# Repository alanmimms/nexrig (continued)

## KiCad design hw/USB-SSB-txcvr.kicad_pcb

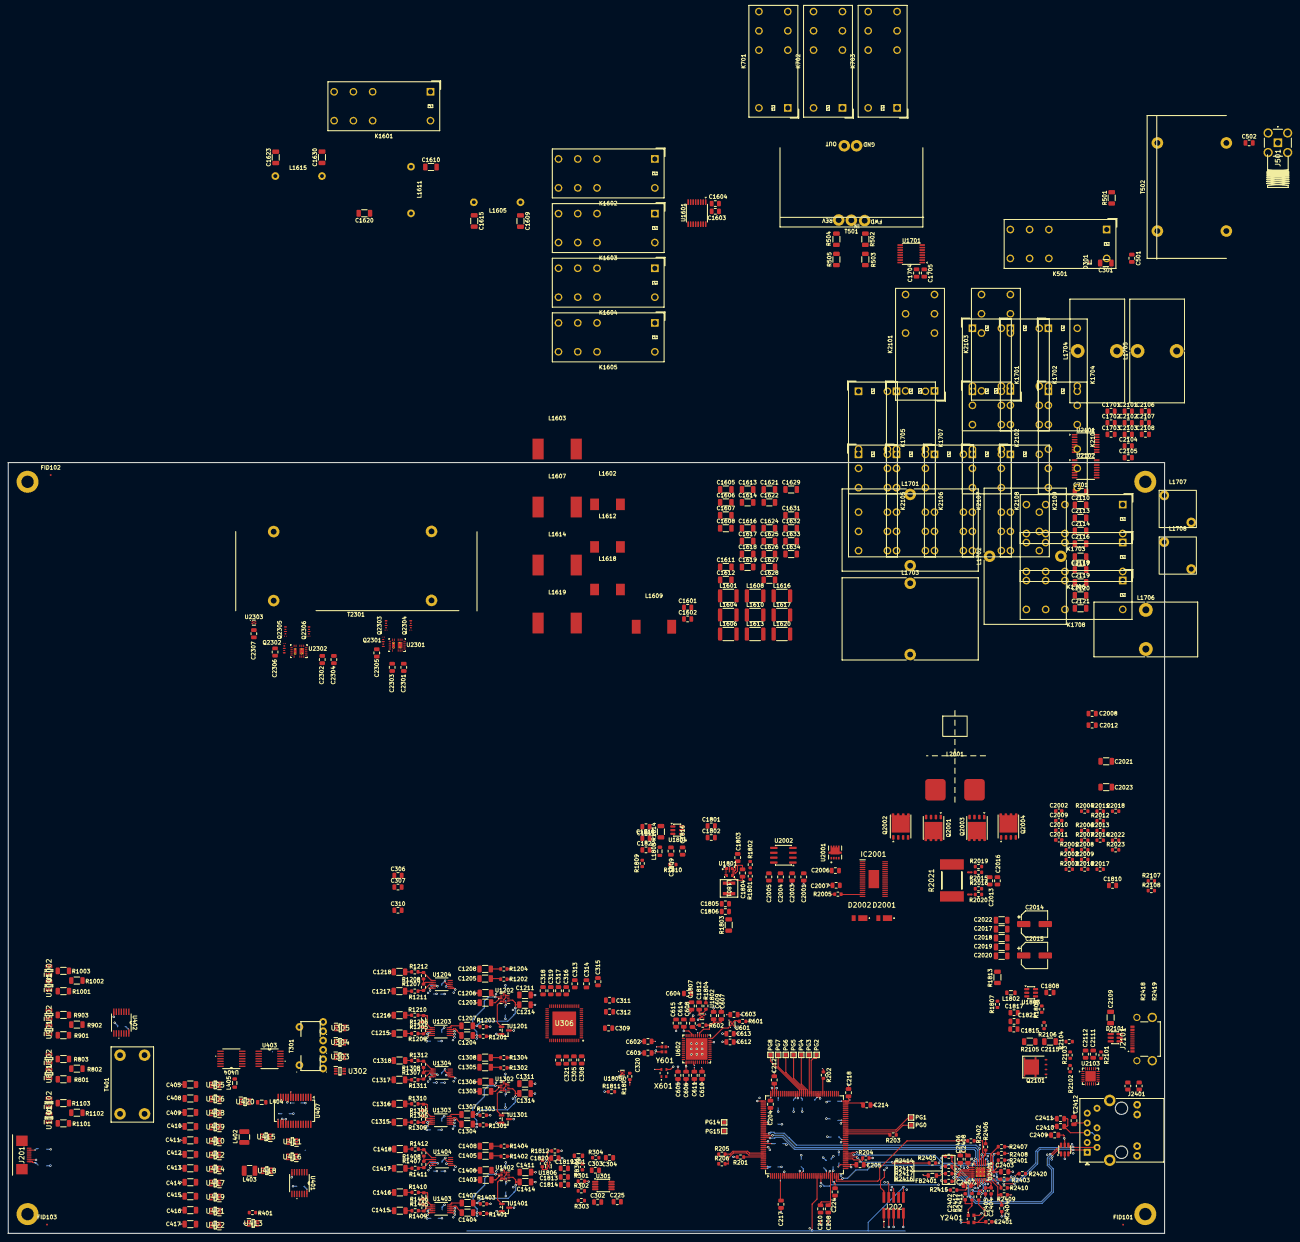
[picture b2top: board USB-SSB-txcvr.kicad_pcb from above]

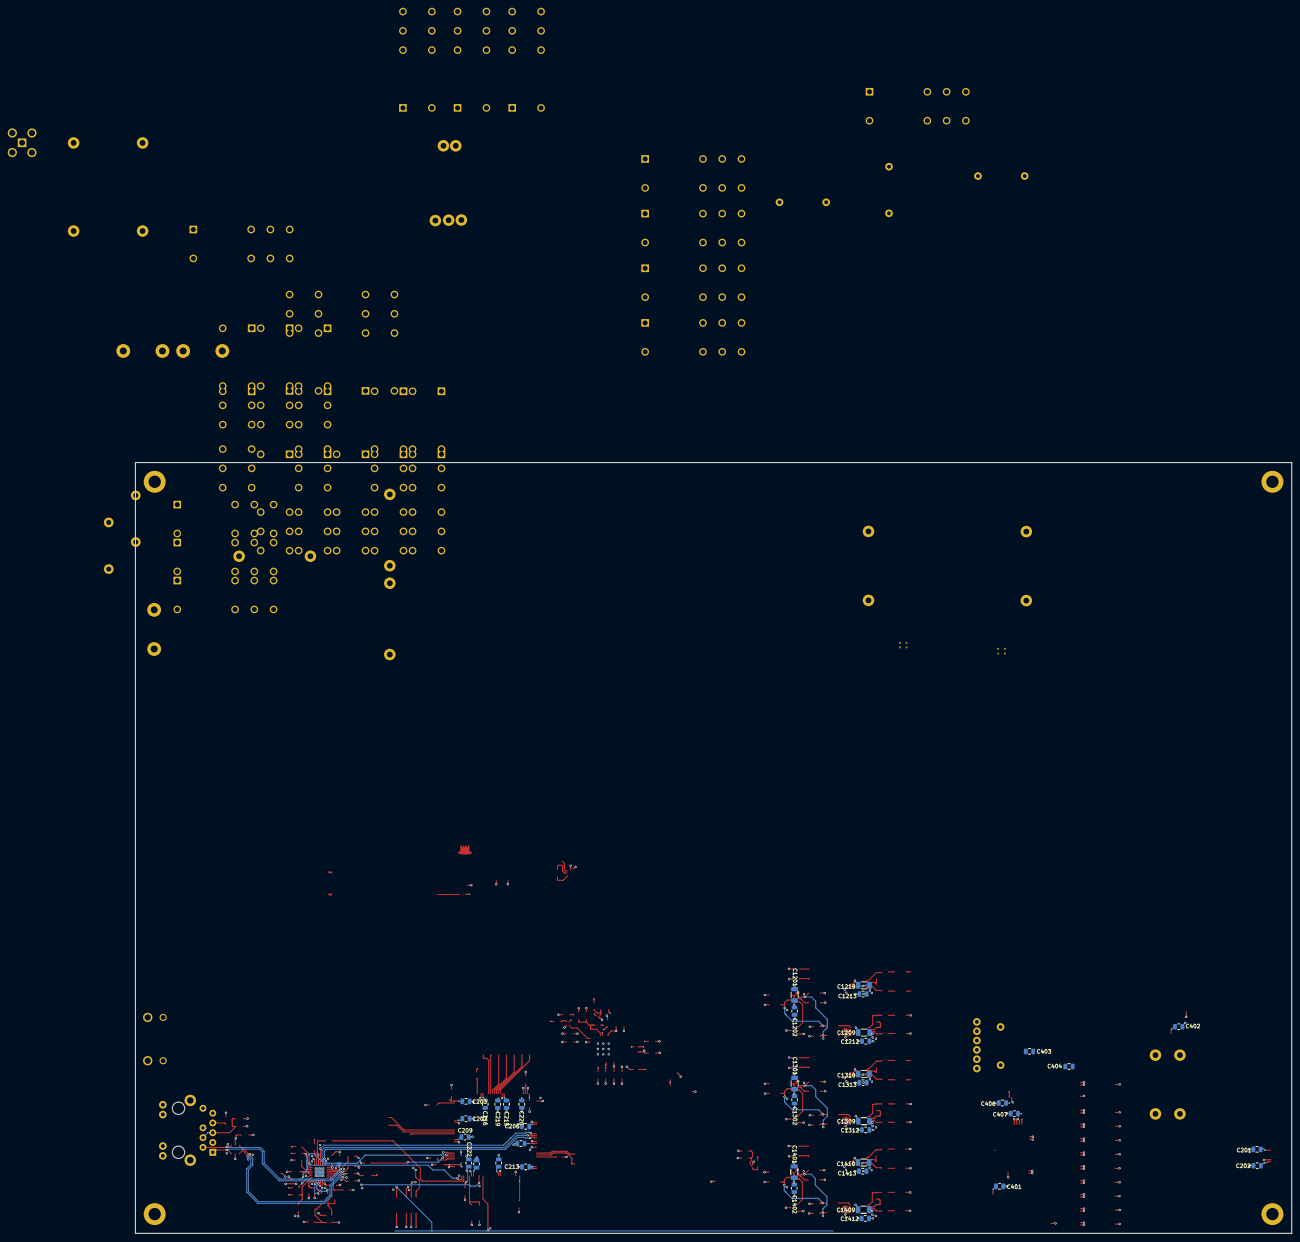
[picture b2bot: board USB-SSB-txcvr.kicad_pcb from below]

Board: 6 copper layers, 300.0 x 200.0 mm, 573 parts (39 on the bottom side), 399 nets.

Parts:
C201, C202, C204, C205, C305, C309, C312, C314, C501, C1601, C1602, C1603, C1701, C1702, C1703, C1704, C1817, C1818, C1821, C1822, C2005, C2101, C2102, C2103, C2104, C2105, C2107, C2406: 10uF; C_0805_2012Metric
C203: 100uF; C_0805_2012Metric
C206, C207, C208, C210, C212, C214, C217, C218, C219, C220, C221, C222, C224, C225, C302, C304, C308, C310, C311, C313, C315, C316, C318, C321, C602, C608, C609, C613, C615, C1202, C1212, C1213, C1302, C1312, C1313, C1402, C1412, C1413, C1804, C1815, C1816, C2003, C2007, C2008, C2012, C2301, C2302, C2403, C2407, C2408, C2409, C2410, C2411: 0.1uF; C_0805_2012Metric
C209, C216, C223, C307, C320, C401, C402, C403, C404, C406, C407, C601, C603, C604, C1803, C1807, C1812, C1813, C1814, C1819, C1820, C2307: 1uF; C_0805_2012Metric
C211, C1604, C1705, C2106, C2108: 100nF; C_0805_2012Metric
C213, C215, C303, C306, C2303, C2304: 2.2uF; C_0805_2012Metric
C301: 1uF 250V; C_1206_3216Metric
C317, C319, C605, C607, C612, C614, C2006, C2111, C2112: 4.7uF; C_0805_2012Metric
C405: 4pF; C_1206_3216Metric
C408: 8pF; C_1206_3216Metric
C409: 16pF; C_1206_3216Metric
C410: 32pF; C_1206_3216Metric
C411: 64pF; C_1206_3216Metric
C412: 128pF; C_1206_3216Metric
C413: 256pF; C_1206_3216Metric
C414: 512pF; C_1206_3216Metric
C415: 1024pF; C_1206_3216Metric
C416: 2048pF; C_1206_3216Metric
C417: 2.2nF; C_1206_3216Metric
C502: 10uF 500V; C_0805_2012Metric
C606: .1uF; C_0805_2012Metric
C610, C2001: 10nF; C_0805_2012Metric
C611: 1nF; C_0805_2012Metric
C701, C1201, C1301, C1401, C2021, C2023: 10uF; C_1206_3216Metric
C1203, C1206, C1211, C1214, C1303, C1306, C1311, C1314, C1403, C1406, C1411, C1414: 2.2uF; C_1206_3216Metric
C1204, C1205, C1207, C1208, C1209, C1210, C1304, C1305, C1307, C1308, C1309, C1310, C1404, C1405, C1407, C1408, C1409, C1410, C2017, C2018, C2019, C2020, C2022: 1uF; C_1206_3216Metric
C1215, C1216, C1217, C1218, C1315, C1316, C1317, C1318, C1415, C1416, C1417, C1418: 3.3nF; C_1206_3216Metric
C1605, C1633: 39pF; C_1206_3216Metric
C1606, C1611, C1621, C1632: 150pF; C_1206_3216Metric
C1607, C1634: 75pF; C_1206_3216Metric
C1608, C1619, C1622, C1631: 27pF; C_1206_3216Metric
C1609, C1630: 360pF; C_1206_3216Metric
C1610, C1620: 330pF; C_1206_3216Metric
C1612, C1629: 62pF; C_1206_3216Metric
C1613, C1628: 33pF; C_1206_3216Metric
C1614, C1626: 24pF; C_1206_3216Metric
C1615, C1623: 300pF; C_1206_3216Metric
C1616, C1624: 120pF; C_1206_3216Metric
C1617, C1627: 68pF; C_1206_3216Metric
C1618, C1625: 36pF; C_1206_3216Metric
C1801: 4.7uF 50V; C_0805_2012Metric
C1802: 0.1uF 50V; C_0805_2012Metric
C1805, C1806: 22uF; C_0805_2012Metric
C1808, C1809, C1810, C1811: 1uF 50V; C_0805_2012Metric
C2002, C2011: 100pF; C_0603_1608Metric
C2004, C2305, C2306: 3.3nF; C_0805_2012Metric
C2009, C2010: 0.22uF; C_0603_1608Metric
C2013: 220pF; C_0805_2012Metric
C2014, C2015: 10uF; CP_Elec_6.3x5.4
C2016: 470pF; C_0805_2012Metric
C2109: 4.7uF 50V; C_1206_3216Metric
C2110: 1280pF; C_1206_3216Metric
C2113: 640pF; C_1206_3216Metric
C2114: 320pF; C_1206_3216Metric
C2115: 0.1uF 50V; C_1206_3216Metric
C2116: 160pF; C_1206_3216Metric
C2117: 80pF; C_1206_3216Metric
C2118: 40pF; C_1206_3216Metric
C2119: 20pF; C_1206_3216Metric
C2120: 10pF; C_1206_3216Metric
C2121: 5pF; C_1206_3216Metric
C2401, C2402: 8.2pF; C_0603_1608Metric
C2404: 1uF; C_0603_1608Metric
C2405: 470pF; C_0603_1608Metric
C2412: 1000pF; C_0805_2012Metric
D301: STS321150B100AH; Infineon_SG-WLL-2-3_0.58x0.28_P0.36mm
D2001, D2002: DFLS1200-7; DFLS12007
D2101: MMQA33VT1G; SC-74-6_1.55x2.9mm_P0.95mm
FB301: 600; L_0603_1608Metric
FB2401: BLM21AG102SN1D; L_0805_2012Metric
FID101, FID102, FID103: Fiducial; Fiducial_0.5mm_Mask2mm
IC2001: LTC3779IFE#PBF; SOP50P640X120-39N
J201: 68710814022
J202: FTSH-105-01-L-DV-K; FTSH10501LDVK
J501: SMA; RFPCSMA27F
J2101: USB C power only; UJ20CHGMSMT4P16TR
J2401: RJ45_Abracon_ARJP11A-MASA-B-A-EMU2; RJ45_Abracon_ARJP11A-MA_Horizontal
K501, K701, K702, K703, K1601, K1602, K1603, K1604, K1605, K1701, K1702, K1703, K1704, K1705, K1706, K1707, K1708, K2101, K2102, K2103, K2104, K2105, K2106, K2107, K2108, K2109: G2RL-2; Relay_DPDT_Omron_G2RL-2
L301: 1.2uH; L_0805_2012Metric
L402: 8.2uH; L_1210_3225Metric
L403: 2.7uH; L_1210_3225Metric
L404: 820nH; L_0805_2012Metric
L405: 270nH; L_0805_2012Metric
L1601, L1604, L1616, L1620: 1.2uH; L_1812_4532Metric
L1602, L1618: 3.3uH; L_Wurth_8.4mm_sq_SMT
L1603, L1607, L1614, L1619: 3.9uH; L_Wurth_12.1mm_sq_SMT
L1605, L1615: 17.4uH; toroid-inductor-t80-2
L1606, L1610, L1617: 1.5uH; L_1812_4532Metric
L1608, L1613: 1uH; L_1812_4532Metric
L1609: 8.2uH; L_Wurth_10.9mm_sq_SMT
L1611: 19.1uH; toroid-inductor-t80-2
L1612: 4.7uH; L_Wurth_8.4mm_sq_SMT
L1701: 64uH; L_Toroid_Vertical_L35.1mm_W21.1mm_P18.50mm_Vishay_TJ6
L1702: 32uH; L_Toroid_Vertical_L35.1mm_W21.1mm_P18.50mm_Vishay_TJ6
L1703: 16uH; L_Toroid_Vertical_L35.1mm_W21.1mm_P18.50mm_Vishay_TJ6
L1704: 8uH; L_Toroid_Vertical_L26.7mm_W14.0mm_P10.16mm_Pulse_D
L1705: 4uH; L_Toroid_Vertical_L26.7mm_W14.0mm_P10.16mm_Pulse_D
L1706: 2uH; L_Toroid_Vertical_L26.7mm_W14.0mm_P10.16mm_Pulse_D
L1707: 1uH; Coilcraft-uni10
L1708: 0.5uH; Coilcraft-uni10
L1801: 2.2uH; IND_XGL4030_COC
L1802: 2.2uH; L_0805_2012Metric
L1803: 3.3uH; L_0805_2012Metric
L2001: 6.8uH; Bourns PQ2614BLA-6R8K
MH101, MH102, MH103, MH104: MountingHole; MountingHole_3.2mm_M3_ISO7380_Pad
NT2001, NT2002: NetTie_2; NetTie-2_SMD_Pad0.5mm
PG201: PG0; TestPoint_Pad_1.0x1.0mm
PG202: PG1; TestPoint_Pad_1.0x1.0mm
PG203: PG2; TestPoint_Pad_1.0x1.0mm
PG204: PG3; TestPoint_Pad_1.0x1.0mm
PG205: PG4; TestPoint_Pad_1.0x1.0mm
PG206: PG5; TestPoint_Pad_1.0x1.0mm
PG207: PG6; TestPoint_Pad_1.0x1.0mm
PG208: PG7; TestPoint_Pad_1.0x1.0mm
PG209: PG8; TestPoint_Pad_1.0x1.0mm
PG210: PG14; TestPoint_Pad_1.0x1.0mm
PG211: PG15; TestPoint_Pad_1.0x1.0mm
Q2001, Q2002, Q2003, Q2004: BSC360N15NS3 G; Infineon_PG-TDSON-8_6.15x5.15mm
Q2101: SQJ433EP; PowerPAK_SO-8L_Single
Q2301, Q2302, Q2303, Q2304, Q2305, Q2306: EPC2207; EPC2207-GaN-FET
R201, R202, R203, R204, R205, R206, R303, R304, R1201, R1202, R1203, R1204, R1205, R1206, R1207, R1208, R1301, R1302, R1303, R1304, R1305, R1306, R1307, R1308, R1401, R1402, R1403, R1404, R1405, R1406, R1407, R1408, R2002, R2005, R2008, R2108, R2401, R2406, R2408, R2409, R2410, R2420: 10k; R_0603_1608Metric
R301, R302, R2012, R2013, R2101, R2106: 1k; R_0603_1608Metric
R401: 6.8; R_0603_1608Metric
R501: 49.9; R_1206_3216Metric
R502, R504: 47k; R_1206_3216Metric
R503, R505: 220; R_1206_3216Metric
R601, R1804, R1805, R1806, R1811, R1812, R2411, R2412: 0; R_0603_1608Metric
R602, R2015, R2016, R2019, R2020, R2104: 100; R_0603_1608Metric
R801, R803, R901, R903, R1001, R1003, R1101, R1103: 34; R_1206_3216Metric
R802, R902, R1002, R1102: 562; R_1206_3216Metric
R1209, R1210, R1211, R1212, R1309, R1310, R1311, R1312, R1409, R1410, R1411, R1412: 330; R_0603_1608Metric
R1801: 60.4k; R_0603_1608Metric
R1802, R2415: 12.1k; R_0603_1608Metric
R1803, R1813, R1814, R2105: 0; R_1206_3216Metric
R1807, R1809, R2003, R2009, R2102, R2107, R2407: 100k; R_0603_1608Metric
R1808: 22.1k; R_0603_1608Metric
R1810: 13.7k; R_0603_1608Metric
R2001: 649k; R_0603_1608Metric
R2004, R2010: 3.53k; R_0603_1608Metric
R2006: 13k; R_0603_1608Metric
R2007: 125k; R_0603_1608Metric
R2011: 107k; R_0603_1608Metric
R2014: 5; R_0603_1608Metric
R2017, R2018, R2022, R2023: 2; R_0603_1608Metric
R2021: 5m; CSS2H3920K5L00F
R2103: 22k; R_0603_1608Metric
R2402, R2403, R2404, R2405: 33; R_0603_1608Metric
R2413, R2414, R2416, R2417: 49.9; R_0603_1608Metric
R2418, R2419: 270; R_0805_2012Metric
T301: 12t primary : 6T #26 trifilar secondary FT37-43; Toroid-1pri-3sec-ft50
T401: 8t bifilar; 200-800-transformer-FT50
T501: 2xFT140-stacked-bruene
T502: 16t:8t bifilar #18AWG FT140-43; 2xFT140-stacked
T2301: 2xFT240-stacked
U201: STM32H753ZIT6; LQFP-144_20x20mm_P0.5mm
U301: OPA1692xDGK; VSSOP-8_3x3mm_P0.65mm
U302: SOT65P220X110-6N
U303, U304, U305, U405, U406, U408, U409, U410, U411, U412, U413, U414, U415, U416, U417, U418, U419, U420, U421, U422, U801, U802, U901, U902, U1001, U1002, U1101, U1102: AS183-92LF; SOT65P220X110-6N
U306: AK5578EN; QFN50P900X900X100-65N
U401, U402, U403, U404: SN74LVC04APW; PW14
U407: MCP23S17_SS; SSOP-28_5.3x10.2mm_P0.65mm
U601: TPS7A2025PDQN; Texas_X2SON-4_1x1mm_P0.65mm
U602: ICE40UP5K-SG48ITR; QFN-48-1EP_7x7mm_P0.5mm_EP5.6x5.6mm
U1201, U1301, U1401: SZNUP1105LT1G; SOT-23
U1202, U1302, U1402: TS3A4751RUCR; TS3A4751-RUC14
U1203, U1204, U1303, U1304, U1403, U1404: MAX9939AUB+T; 21-0061L_MXM
U1601, U1701, U2101, U2102: TLC6C598PW; TSSOP-16_4.4x5mm_P0.65mm
U1801: LMR43610R3RPER; RPE0009A-MFG
U1802: TPS7A2012DQN; Texas_X2SON-4_1x1mm_P0.65mm
U1803, U1804: LMR51430; SOT-23-6
U1805: TPS7A92050DBVR; Texas_X2SON-4_1x1mm_P0.65mm
U1806: TPS7A2033DQN; Texas_X2SON-4_1x1mm_P0.65mm
U2001: NVTFS6H888NLTAG; WDFN_8NLTAG_ONS
U2002: TLV9062xD; SOIC-8_3.9x4.9mm_P1.27mm
U2103: STUSB4500QTR; QFN-24-1EP_4x4mm_P0.5mm_EP2.7x2.7mm
U2301, U2302: LMG1210RVRR; RVR0019A
U2303: TMP110D; Texas_X2SON-5_0.8x0.8mm_P0.48mm
U2401: LAN8742A; VQFN-24-1EP_4x4mm_P0.5mm_EP2.5x2.5mm_ThermalVias
U2402: USBLC6-4SC6; SOT-23-6
X601: XC8102AA01NR-G; XC8102AA01NRG
Y601: ECS-TXO-2016-33-400-TR; ECSTXO201633400TR
Y2401: ECS-250-8-37B2-RWN; ECS2033250BN

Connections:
+2.7V: C2112.1, U2103.23 (VREG_2V7)
+3.3V: C201.1, C202.1, C203.1, C204.1, C205.1, C206.1, C207.1, C208.1, C210.1, C212.1, C214.1, C216.1, C217.1, C218.1, C219.1, C220.1, C221.1, C222.1, C224.1, C310.1, C316.2, C317.2, C320.1, C321.1, C401.2, C402.2, C403.2, C404.2, C406.1, C407.1, C601.1, C602.1, C603.1, C1603.2, C1604.2, C1704.2, C1705.2, C1807.1, C2104.2, C2106.2, C2107.2, C2108.2, C2307.1, C2403.1, FB2401.1, J201.2, J201.8, J202.1 (VTref), R202.1, R203.1, R204.1, R205.1, R601.1, R1805.1, R1806.1, R1813.1, R2005.1, R2108.1, R2406.2, R2407.2, R2408.2, R2409.2, R2410.2, U201.6 (VBAT), U201.17 (VDD), U201.30 (VDD), U201.39 (VDD), U201.52 (VDD), U201.62 (VDD), U201.72 (VDD), U201.84 (VDD), U201.95 (VDD33USB), U201.108 (VDD), U201.121 (VDD), U201.131 (VDD), U201.143 (PDR_ON), U201.144 (VDD), U302.5 (V), U306.25 (TVDD), U306.30 (PW1), U306.31 (PW2), U306.32 (MSN), U306.51 (TDM0), U306.52 (TDM1), U306.54 (I2C), U306.57 (LDOE), U306.58 (ODP), U401.14 (VCC), U402.14 (VCC), U403.14 (VCC), U404.14 (VCC), U407.9 (VDD), U407.15 (A0), U601.4 (IN), U1601.1 (VCC), U1601.7 (~CLR), U1601.8 (~G), U1701.1 (VCC), U1701.7 (~CLR), U1701.8 (~G), U1802.4 (IN), U2101.1 (VCC), U2101.7 (~CLR), U2101.8 (~G), U2102.1 (VCC), U2102.7 (~CLR), U2102.8 (~G), U2303.5 (V+), U2401.9 (VDDIO), X601.4 (VIN), Y601.1 (TRI-STATE), Y601.4 (VDD)
+3.3VA: C223.1, C225.1, C1201.1, C1202.1, C1301.1, C1302.1, C1401.1, C1402.1, R301.2, R1812.1, U201.33 (VDDA), U1201.3, U1202.14 (V+), U1301.3, U1302.14 (V+), U1401.3, U1402.14 (V+)
+3.3VFPGAIO: C605.1, C606.1, C612.1, C613.1, C614.1, C615.1, U602.1 (VCCIO_2), U602.22 (SPI_VCCIO1), U602.33 (VCCIO_0), X601.3 (VOUT)
+5V: C501.1, C701.2, C1601.1, C1602.1, C1701.1, C1702.1, C1703.1, C2101.1, C2102.1, C2103.1, C2105.2, C2301.1, C2302.1, C2303.1, C2304.1, K501.12, Q2301.2 (S), Q2301.4 (S), Q2302.2 (S), Q2302.4 (S), R1814.1, U2301.2 (VIN), U2301.4 (VCC), U2301.5 (DHL), U2301.6 (DLH), U2302.2 (VIN), U2302.4 (VCC), U2302.5 (DHL), U2302.6 (DLH)
+5VA: C302.1, C1209.1, C1210.1, C1212.1, C1213.1, C1309.1, C1310.1, C1312.1, C1313.1, C1409.1, C1410.1, C1412.1, C1413.1, C2001.1, C2003.1, C2005.1, R1811.1, U301.8 (V+), U306.2 (AVDD1), U306.15 (AVDD2), U1203.9 (VCC), U1204.9 (VCC), U1303.9 (VCC), U1304.9 (VCC), U1403.9 (VCC), U1404.9 (VCC), U2002.8 (V+)
+6V: C1813.1, C1814.1, R1803.1, U1805.4 (IN), U1806.4 (IN)
/FPGA/CDONE: U201.141 (PE0), U602.7 (CDONE)
/FPGA/Ctrl.audioReset: R206.1, U201.42 (PA6), U306.28 (PDN)
/FPGA/Ctrl.audioSCL: R202.2, U201.81 (PD12), U306.45 (CKS2/SCL/CCLK)
/FPGA/Ctrl.audioSDA: R203.2, U201.55 (PF15), U306.43 (CKS0/SDA/CDTI)
/FPGA/Ctrl.enFPGAIOVdd: U201.18 (PF6), X601.1 (CE)
/FPGA/Ctrl.enable5V: U201.26 (PC0), U1804.5 (EN)
/FPGA/Ctrl.enable6V: U201.53 (PF13), U1801.3 (EN_UVLO)
/FPGA/Ctrl.qsdBCLK: U201.4 (PE5), U306.33 (BICK/DCLK)
/FPGA/Ctrl.qsdData: U201.5 (PE6), U306.36 (SDTO1/DSDOL2)
/FPGA/Ctrl.qsdMCLK: U306.24 (MCLK), U602.12 (IOB_22a)
/FPGA/Ctrl.qsdMOSI: U201.67 (PE14), U1203.2 (DIN), U1204.2 (DIN), U1303.2 (DIN), U1304.2 (DIN), U1403.2 (DIN), U1404.2 (DIN)
/FPGA/Ctrl.qsdNSS: U201.64 (PE11), U1203.10 (*CS), U1204.10 (*CS), U1303.10 (*CS), U1304.10 (*CS), U1403.10 (*CS), U1404.10 (*CS)
/FPGA/Ctrl.qsdPh0a: U602.6 (IOB_13b), U1402.1 (NO1)
/FPGA/Ctrl.qsdPh1a: U602.21 (IOB_23b), U1202.1 (NO1)
/FPGA/Ctrl.qsdPh2a: U602.45 (IOB_5b), U1302.1 (NO1)
/FPGA/Ctrl.qsdPh2b: U602.2 (IOB_6a), U602.9 (IOB_16a), U602.13 (IOB_24a), U1202.3 (NO2), U1302.3 (NO2), U1402.3 (NO2)
/FPGA/Ctrl.qsdPh2c: U602.4 (IOB_8a), U602.10 (IOB_18a), U602.20 (IOB_25b_G3), U1202.8 (NO3), U1302.8 (NO3), U1402.8 (NO3)
/FPGA/Ctrl.qsdPh2d: U602.3 (IOB_9b), U602.11 (IOB_20a), U602.19 (IOB_29b), U1202.11 (NO4), U1302.11 (NO4), U1402.11 (NO4)
/FPGA/Ctrl.qsdSCK: U201.1 (PE2), U1203.1 (SCLK), U1204.1 (SCLK), U1303.1 (SCLK), U1304.1 (SCLK), U1403.1 (SCLK), U1404.1 (SCLK)
/FPGA/Ctrl.qsdWCLK: U201.3 (PE4), U306.34 (LRCK/DSDOL1)
/FPGA/Ctrl.switchMOSI: U201.29 (PC3_C), U2101.2 (SER_IN)
/FPGA/Ctrl.switchRCK: U201.10 (PF0), U1601.10 (RCK), U1701.10 (RCK), U2101.10 (RCK), U2102.10 (RCK)
/FPGA/Ctrl.switchSCK: U201.69 (PB10), U1601.15 (SRCK), U1701.15 (SRCK), U2101.15 (SRCK), U2102.15 (SRCK)
/FPGA/Ctrl.tmpSCL: R204.2, U201.136 (PB6), U2103.7 (SCL)
/FPGA/Ctrl.tmpSDA: R205.2, U201.137 (PB7), U2103.8 (SDA)
/FPGA/Ctrl.txBCLK: U201.20 (PF8), U602.43 (IOT_49a)
/FPGA/Ctrl.txData: U201.2 (PE3), U602.42 (IOT_51a)
/FPGA/Ctrl.txMCLK: U201.19 (PF7), U602.36 (IOT_48b)
/FPGA/Ctrl.txWCLK: U201.21 (PF9), U602.38 (IOT_50b)
/FPGA/Ctrl.usbPOK2: U201.22 (PF10), U2103.20 (POWER_OK2)
/FPGA/Ctrl.usbPOK3: U201.49 (PF11), U2103.14 (POWER_OK3)
/FPGA/Ctrl.usbReset: R2107.1, U2103.6 (RESET)
/FPGA/Ctrl.usbnALERT: R2108.2, U201.54 (PF14), U2103.19 (ALERT)
/FPGA/FPGA.MISO: U201.112 (PC11), U602.14 (IOB_32a_SPI_SO)
/FPGA/FPGA.MOSI: U201.48 (PB2), U602.17 (IOB_33b_SPI_SI)
/FPGA/FPGA.NSS: U201.110 (PA15), U602.16 (IOB_35b_SPI_SS)
/FPGA/FPGA.RESET: U201.68 (PE15), U602.8 (~CRESET)
/FPGA/FPGA.SCK: U201.111 (PC10), U602.15 (IOB_34a_SPI_SCK)
/FPGA/PAI+: U602.25 (IOT_36b), U2301.18 (HI_EN)
/FPGA/PAI-: U602.23 (IOT_37a), U2301.19 (PWM_LI)
/FPGA/PAQ+: U602.27 (IOT_38b), U2302.18 (HI_EN)
/FPGA/PAQ-: U602.26 (IOT_39a), U2302.19 (PWM_LI)
/FPGA/STM32clock: U201.23 (PH0-OSC_IN), U602.18 (IOB_31b)
/FPGA/VPP2V5: C604.1, U601.1 (OUT), U602.24 (VPP_2V5)
/Power/FPGA1V2enable: U201.142 (PE1), U1802.3 (EN)
/Power/Tx EER Envelope Buck-Boost/BG1: IC2001.1 (BG1), R2018.1
/Power/Tx EER Envelope Buck-Boost/BG2: IC2001.19 (BG2), R2023.1
/Power/Tx EER Envelope Buck-Boost/FB: C2011.2, IC2001.10 (VFB), R2011.2, U2002.1
/Power/Tx EER Envelope Buck-Boost/IAVGSNSN: C2016.2, R2019.1
/Power/Tx EER Envelope Buck-Boost/IAVGSNSP: C2016.1, IC2001.26 (IAVGSNSP), IC2001.28 (IAVGSNSN), R2020.1
/Power/Tx EER Envelope Buck-Boost/SENSEN: C2013.1, IC2001.12 (SENSEN), R2016.1
/Power/Tx EER Envelope Buck-Boost/SENSEP: C2013.2, IC2001.11 (SENSEP), R2015.1
/Power/Tx EER Envelope Buck-Boost/SW1: C2010.1, IC2001.38 (SW1), L2001.1, Q2001.1 (S), Q2001.2 (S), Q2001.3 (S), Q2002.5 (D)
/Power/Tx EER Envelope Buck-Boost/SW2: C2009.2, IC2001.20 (SW2), L2001.2, Q2003.1 (S), Q2003.2 (S), Q2003.3 (S), Q2004.5 (D)
/Power/Tx EER Envelope Buck-Boost/TG1: IC2001.37 (TG1), R2017.1
/Power/Tx EER Envelope Buck-Boost/TG2: IC2001.21 (TG2), R2022.1
/Power/TxAmplitude: R2008.1, U201.40 (PA4)
/Power/TxEnable: IC2001.24 (RUN), U201.103 (PA11)
/Power/TxPGOOD: IC2001.18 (PGOOD), R2005.2, U201.96 (PC6)
/Power/USB-PD/CC1: D2101.4 (K_3), J2101.A5 (CC1), U2103.1 (CC1DB), U2103.2 (CC1)
/Power/USB-PD/CC2: D2101.6 (K_4), J2101.B5 (CC2), U2103.4 (CC2), U2103.5 (CC2DB)
/Power/USB-PD/VBUS_DISCH: R2101.2, U2103.18 (VBUS_VS_DISCH)
/Power/scaledEERVdd: U201.50 (PF12), U2002.6 (-), U2002.7
/Rx Front End/Clipper, Attenuator, Preselector/C0: U404.5 (3A), U405.4 (V1), U407.21 (GPA0)
/Rx Front End/Clipper, Attenuator, Preselector/C1: U404.9 (4A), U406.4 (V1), U407.22 (GPA1)
/Rx Front End/Clipper, Attenuator, Preselector/C2: U404.11 (5A), U407.23 (GPA2), U408.4 (V1)
/Rx Front End/Clipper, Attenuator, Preselector/C3: U404.13 (6A), U407.24 (GPA3), U409.4 (V1)
/Rx Front End/Clipper, Attenuator, Preselector/C4: U403.1 (1A), U407.25 (GPA4), U410.4 (V1)
/Rx Front End/Clipper, Attenuator, Preselector/C5: U403.3 (2A), U407.26 (GPA5), U412.4 (V1)
/Rx Front End/Clipper, Attenuator, Preselector/C6: U403.5 (3A), U407.27 (GPA6), U414.4 (V1)
/Rx Front End/Clipper, Attenuator, Preselector/C7: U403.13 (6A), U407.28 (GPA7), U417.4 (V1)
/Rx Front End/Clipper, Attenuator, Preselector/C8: U403.11 (5A), U407.1 (GPB0), U419.4 (V1)
/Rx Front End/Clipper, Attenuator, Preselector/C9: U401.3 (2A), U407.2 (GPB1), U421.4 (V1)
/Rx Front End/Clipper, Attenuator, Preselector/C10: U403.9 (4A), U407.3 (GPB2), U422.4 (V1)
/Rx Front End/Clipper, Attenuator, Preselector/Ctrl.atten3dB: U402.9 (4A), U1101.4 (V1), U1102.4 (V1)
/Rx Front End/Clipper, Attenuator, Preselector/Ctrl.atten6dB: U402.11 (5A), U801.4 (V1), U802.4 (V1)
/Rx Front End/Clipper, Attenuator, Preselector/Ctrl.atten12dB: U402.5 (3A), U901.4 (V1), U902.4 (V1)
/Rx Front End/Clipper, Attenuator, Preselector/Ctrl.atten24dB: U402.3 (2A), U1001.4 (V1), U1002.4 (V1)
/Rx Front End/Clipper, Attenuator, Preselector/L1: U401.13 (6A), U407.5 (GPB4), U413.4 (V1)
/Rx Front End/Clipper, Attenuator, Preselector/L1L2: U401.11 (5A), U407.4 (GPB3), U411.4 (V1), U416.4 (V1)
/Rx Front End/Clipper, Attenuator, Preselector/L2: U401.9 (4A), U407.6 (GPB5), U415.4 (V1)
/Rx Front End/Clipper, Attenuator, Preselector/L3: U404.1 (1A), U407.7 (GPB6), U418.4 (V1)
/Rx Front End/Clipper, Attenuator, Preselector/L4: U404.3 (2A), U407.8 (GPB7), U420.4 (V1)
/Rx Front End/Clipper, Attenuator, Preselector/RxZ200: C301.2, D301.1 (A1), U1001.5 (J1)
/Rx Front End/Clipper, Attenuator, Preselector/Tpad 3/in: U802.5 (J1), U1101.5 (J1)
/Rx Front End/Clipper, Attenuator, Preselector/Tpad 3/out: T401.1, U1102.5 (J1)
/Rx Front End/Clipper, Attenuator, Preselector/Tpad 12/in: U901.5 (J1), U1002.5 (J1)
/Rx Front End/Clipper, Attenuator, Preselector/Tpad 12/out: U801.5 (J1), U902.5 (J1)
/Rx Front End/Clipper, Attenuator, Preselector/n3dB: U402.8 (4Y), U1101.6 (V2), U1102.6 (V2)
/Rx Front End/Clipper, Attenuator, Preselector/n6dB: U402.10 (5Y), U801.6 (V2), U802.6 (V2)
/Rx Front End/Clipper, Attenuator, Preselector/n12dB: U402.6 (3Y), U901.6 (V2), U902.6 (V2)
/Rx Front End/Clipper, Attenuator, Preselector/n24dB: U402.4 (2Y), U1001.6 (V2), U1002.6 (V2)
/Rx Front End/Clipper, Attenuator, Preselector/nC0: U404.6 (3Y), U405.6 (V2)
/Rx Front End/Clipper, Attenuator, Preselector/nC1: U404.8 (4Y), U406.6 (V2)
/Rx Front End/Clipper, Attenuator, Preselector/nC2: U404.10 (5Y), U408.6 (V2)
/Rx Front End/Clipper, Attenuator, Preselector/nC3: U404.12 (6Y), U409.6 (V2)
/Rx Front End/Clipper, Attenuator, Preselector/nC4: U403.2 (1Y), U410.6 (V2)
/Rx Front End/Clipper, Attenuator, Preselector/nC5: U403.4 (2Y), U412.6 (V2)
/Rx Front End/Clipper, Attenuator, Preselector/nC6: U403.6 (3Y), U414.6 (V2)
/Rx Front End/Clipper, Attenuator, Preselector/nC7: U403.12 (6Y), U417.6 (V2)
/Rx Front End/Clipper, Attenuator, Preselector/nC8: U403.10 (5Y), U419.6 (V2)
/Rx Front End/Clipper, Attenuator, Preselector/nC9: U401.4 (2Y), U421.6 (V2)
/Rx Front End/Clipper, Attenuator, Preselector/nC10: U403.8 (4Y), U422.6 (V2)
/Rx Front End/Clipper, Attenuator, Preselector/nL1: U401.12 (6Y), U413.6 (V2)
/Rx Front End/Clipper, Attenuator, Preselector/nL1L2: U401.10 (5Y), U411.6 (V2), U416.6 (V2)
/Rx Front End/Clipper, Attenuator, Preselector/nL2: U401.8 (4Y), U415.6 (V2)
/Rx Front End/Clipper, Attenuator, Preselector/nL3: U404.2 (1Y), U418.6 (V2)
/Rx Front End/Clipper, Attenuator, Preselector/nL4: U404.4 (2Y), U420.6 (V2)
/Rx Front End/Clipper, Attenuator, Preselector/rxPreselOut: T301.1 (IN+), T401.3, U405.1 (J3), U406.1 (J3), U408.1 (J3), U409.1 (J3), U410.1 (J3), U412.1 (J3), U413.3 (J2), U414.1 (J3), U415.3 (J2), U417.1 (J3), U418.3 (J2), U419.1 (J3), U420.3 (J2), U421.1 (J3), U422.1 (J3)
/Rx Front End/Ctrl.breune: U302.1, U303.6 (V2), U304.6 (V2), U305.6 (V2)
/Rx Front End/QSD0/rfIn: U303.5 (J1), U1401.1, U1402.5 (IN2), U1402.6 (IN3), U1402.12 (IN4), U1402.13 (IN1)
/Rx Front End/QSD1/rfIn: U304.5 (J1), U1201.1, U1202.5 (IN2), U1202.6 (IN3), U1202.12 (IN4), U1202.13 (IN1)
/Rx Front End/QSD2/rfIn: U305.5 (J1), U1301.1, U1302.5 (IN2), U1302.6 (IN3), U1302.12 (IN4), U1302.13 (IN1)
/Rx Front End/RxI0n: C1416.1, R1410.2
/Rx Front End/RxI0p: C1415.1, R1409.2, U306.59 (AIN1P)
/Rx Front End/RxI1n: C1216.1, R1210.2, U306.4 (AIN3N)
/Rx Front End/RxI1p: C1215.1, R1209.2, U306.3 (AIN3P)
/Rx Front End/RxI2n: C1316.1, R1310.2, U306.10 (AIN5N)
/Rx Front End/RxI2p: C1315.1, R1309.2, U306.9 (AIN5P)
/Rx Front End/RxQ0n: C1418.1, R1412.2
/Rx Front End/RxQ0p: C1417.1, R1411.2, U306.64 (AIN2P)
/Rx Front End/RxQ1n: C1218.1, R1212.2, U306.7 (AIN4N)
/Rx Front End/RxQ1p: C1217.1, R1211.2, U306.8 (AIN4P)
/Rx Front End/RxQ2n: C1318.1, R1312.2, U306.13 (AIN6N)
/Rx Front End/RxQ2p: C1317.1, R1311.2, U306.14 (AIN6P)
/Rx Front End/VREF1: C305.1, C308.1, U306.62 (VREFH1)
/Rx Front End/VREF2: C309.1, C311.1, U306.6 (VREFH2)
/Rx Front End/VREF3: C312.1, C313.1, U306.11 (VREFH3)
/Rx Front End/VREF4: C314.1, C315.1, U306.19 (VREFH4)
/Rx Front End/nBruene: U302.6, U303.4 (V1), U304.4 (V1), U305.4 (V1)
/Rx Front End/txFwd: R502.2, R503.1, U303.1 (J3), U305.1 (J3)
/Rx Front End/txRev: R504.2, R505.1, U304.1 (J3)
/Tx Chain/Antenna Tuner/Tuner Capacitors/bypass: K701.12, U2102.6 (DRAIN3)
/Tx Chain/Antenna Tuner/Tuner Capacitors/config1: K702.12, U2102.4 (DRAIN1)
/Tx Chain/Antenna Tuner/Tuner Capacitors/config2: K703.12, U2102.5 (DRAIN2)
/Tx Chain/Antenna Tuner/Tuner Capacitors/serOut: U1701.2 (SER_IN), U2102.9 (SER_OUT)
/Tx Chain/tunerSerOut: U1601.2 (SER_IN), U1701.9 (SER_OUT)
/microcontroller/BOOT0: R201.1, U201.138 (BOOT0)
/microcontroller/EthCLK: R2402.1, U201.35 (PA1)
/microcontroller/EthCRS_DV: R2405.1, U201.43 (PA7)
/microcontroller/EthMDC: U201.27 (PC1), U2401.13 (MDC)
/microcontroller/EthMDIO: R2407.1, U201.36 (PA2), U2401.12 (MDIO)
/microcontroller/EthRXD0: R2403.1, U201.44 (PC4)
/microcontroller/EthRXD1: R2404.1, U201.45 (PC5)
/microcontroller/EthTXD0: U201.128 (PG13), U2401.17 (TXD0)
/microcontroller/EthTXD1: U201.127 (PG12), U2401.18 (TXD1)
/microcontroller/EthTxEnable: U201.126 (PG11), U2401.16 (TXEN)
/microcontroller/Ethernet/EthRx+: J2401.3 (RD+), R2416.2, U2401.23 (RXP), U2402.1 (I/O1)
/microcontroller/Ethernet/EthRx-: J2401.6 (RD-), R2417.2, U2401.22 (RXN), U2402.6 (I/O4)
/microcontroller/Ethernet/EthTx+: J2401.1 (TD+), R2413.2, U2401.21 (TXP), U2402.3 (I/O2)
/microcontroller/Ethernet/EthTx-: J2401.2 (TD-), R2414.2, U2401.20 (TXN), U2402.4 (I/O3)
/microcontroller/Ethernet/EthVDDA: C2406.1, C2407.1, C2408.1, C2409.1, FB2401.2, R2413.1, R2414.1, R2416.1, R2417.1, U2401.1 (VDD2A), U2401.19 (VDD1A), U2402.5 (VBUS)
/microcontroller/Ethernet/LEDGA: J2401.13, R2420.1, U2401.2 (LED2/~INTSEL)
/microcontroller/Ethernet/LEDYA: J2401.11, U2401.3 (LED1/REGOFF)
/microcontroller/SWCL: J202.4 (SWCLK/TCK), U201.109 (PA14)
/microcontroller/SWDIO: J202.2 (SWDIO/TMS), U201.105 (PA13)
/microcontroller/SWO: J202.6 (SWO/TDO), U201.133 (PB3)
/microcontroller/VREF: C209.1, C211.1, U201.32 (VREF+)
/microcontroller/dispDC: J201.5, U201.66 (PE13)
/microcontroller/dispMOSI: J201.4, U201.123 (PD7)
/microcontroller/dispNSS: J201.1, U201.125 (PG10)
/microcontroller/dispRESET: J201.6, U201.65 (PE12)
/microcontroller/dispSCK: J201.3, U201.41 (PA5)
FPGA1V2: C608.2, C610.2, C611.2, R602.1, R1804.1, U602.5 (VCC), U602.30 (VCC)
GND: C201.2, C202.2, C203.2, C204.2, C205.2, C206.2, C207.2, C208.2, C209.2, C210.2, C211.2, C212.2, C213.2, C214.2, C215.2, C216.2, C217.2, C218.2, C219.2, C220.2, C221.2, C222.2, C223.2, C224.2, C225.2, C302.2, C303.2, C304.2, C305.2, C306.2, C307.1, C308.2, C309.2, C310.2, C311.2, C312.2, C313.2, C314.2, C315.2, C316.1, C317.1, C318.1, C319.1, C320.2, C321.2, C401.1, C402.1, C403.1, C404.1, C405.2, C406.2, C407.2, C408.2, C409.2, C410.2, C411.2, C412.2, C413.2, C414.2, C415.2, C416.2, C417.2, C501.2, C601.2, C602.2, C603.2, C604.2, C605.2, C606.2, C607.1, C608.1, C609.1, C610.1, C611.1, C612.2, C613.2, C614.2, C615.2, C701.1, C1201.2, C1202.2, C1203.2, C1206.2, C1209.2, C1210.2, C1211.2, C1212.2, C1213.2, C1214.2, C1215.2, C1216.2, C1217.2, C1218.2, C1301.2, C1302.2, C1303.2, C1306.2, C1309.2, C1310.2, C1311.2, C1312.2, C1313.2, C1314.2, C1315.2, C1316.2, C1317.2, C1318.2, C1401.2, C1402.2, C1403.2, C1406.2, C1409.2, C1410.2, C1411.2, C1412.2, C1413.2, C1414.2, C1415.2, C1416.2, C1417.2, C1418.2, C1601.2, C1602.2, C1603.1, C1604.1, C1605.2, C1606.2, C1607.2, C1608.2, C1609.2, C1610.2, C1611.2, C1612.2, C1613.2, C1614.2, C1615.2, C1616.2, C1617.2, C1618.2, C1619.2, C1620.2, C1621.2, C1622.2, C1623.2, C1624.2, C1625.2, C1626.2, C1627.2, C1628.2, C1629.2, C1630.2, C1631.2, C1632.2, C1633.2, C1634.2, C1701.2, C1702.2, C1703.2, C1704.1, C1705.1, C1801.2, C1802.2, C1803.2, C1805.2, C1806.2, C1807.2, C1808.2, C1809.2, C1810.2, C1811.2, C1812.2, C1813.2, C1814.2, C1817.2, C1818.2, C1819.2, C1820.2, C1821.2, C1822.2, C2001.2, C2002.2, C2003.2, C2004.2, C2005.2, C2006.2, C2007.2, C2008.2, C2012.1, C2014.2, C2015.2, C2017.2, C2018.2, C2019.2, C2020.2, C2021.2, C2022.2, C2023.2, C2101.2, C2102.2, C2103.2, C2104.1, C2105.1, C2106.1, C2107.1, C2108.1, C2109.2, C2111.2, C2112.2, C2301.2, C2302.2, C2303.2, C2304.2, C2307.2, C2401.1, C2402.1, C2403.2, C2404.2, C2405.2, C2406.2, C2407.2, C2408.2, C2409.2, C2410.2, C2411.2, C2412.2, D301.2 (A2), D2101.2 (A_1), D2101.5 (A_2), IC2001.4 (SGND_1), IC2001.5 (EXTVCC), IC2001.14 (SGND_2), IC2001.16 (PLLIN), IC2001.23 (NP_1), IC2001.25 (NP_2), IC2001.27 (NP_3), IC2001.29 (NP_4), IC2001.31 (NP_5), IC2001.33 (NP_6), IC2001.35 (NP_7), IC2001.39 (PGND), J201.7, J201.MP1, J201.MP2, J202.3 (GND), J202.5 (GND), J202.9 (GNDDetect), J501.2 (Ext), J501.3 (Ext), J501.4 (Ext), J501.5 (Ext), J2101.1 (MH1), J2101.2 (MH2), J2101.3 (MH3), J2101.4 (MH4), J2101.A1 (GND_1), J2101.B1 (GND_2), J2401.SH, L404.2, L405.2, MH101.1, MH102.1, MH103.1, MH104.1, NT2002.2, Q2304.3 (S), Q2304.4 (S), Q2304.6 (S), Q2306.3 (S), Q2306.4 (S), Q2306.6 (S), R201.2, R206.2, R302.1, R401.2, R501.2, R503.2, R505.2, R802.2, R902.2, R1002.2, R1102.2, R1201.2, R1202.2, R1203.2, R1204.2, R1301.2, R1302.2, R1303.2, R1304.2, R1401.2, R1402.2, R1403.2, R1404.2, R1802.1, R1808.1, R1810.1, R2002.2, R2004.1, R2007.2, R2010.1, R2021.1, R2107.2, R2401.1, R2415.1, R2418.2, R2419.2, R2420.2, T301.2 (IN-), T401.2, T401.4, T501.3, T502.1, T502.3, T2301.4, U201.8 (PC14-OSC32_IN), U201.16 (VSS), U201.31 (VSSA), U201.38 (VSS), U201.51 (VSS), U201.61 (VSS), U201.83 (VSS), U201.94 (VSS), U201.107 (VSS), U201.120 (VSS), U201.130 (VSS), U301.4 (V-), U302.2 (G), U303.2 (GND), U304.2 (GND), U305.2 (GND), U306.1 (AVSS1), U306.5 (VREFL2), U306.12 (VREFL3), U306.16 (AVSS2), U306.20 (VREFL4), U306.26 (DVSS), U306.29 (PW0), U306.44 (CKS1/CAD0_I2C/CSN), U306.46 (CKS3/CAD1), U306.47 (SLOW/DCKB), U306.48 (SD/PMOD), U306.49 (DIF0/DSDSEL0), U306.50 (DIF1/DSDSEL1), U306.53 (PSN/CAD0_SP1), U306.55 (DP), U306.56 (DCKS/HPFE), U306.60 (AIN1N), U306.61 (VREFL1), U306.63 (AIN2N), U306.65 (THERMAL_PAD), U401.7 (GND), U402.7 (GND), U403.7 (GND), U404.7 (GND), U405.2 (GND), U405.3 (J2), U406.2 (GND), U406.3 (J2), U407.10 (VSS), U407.16 (A1), U407.17 (A2), U408.2 (GND), U408.3 (J2), U409.2 (GND), U409.3 (J2), U410.2 (GND), U410.3 (J2), U411.1 (J3), U411.2 (GND), U412.2 (GND), U412.3 (J2), U413.2 (GND), U414.2 (GND), U414.3 (J2), U415.1 (J3), U415.2 (GND), U416.1 (J3), U416.2 (GND), U417.2 (GND), U417.3 (J2), U418.1 (J3), U418.2 (GND), U419.2 (GND), U419.3 (J2), U420.1 (J3), U420.2 (GND), U421.2 (GND), U421.3 (J2), U422.2 (GND), U422.3 (J2), U601.2 (GND), U601.5 (Pad), U602.49 (GND), U801.2 (GND), U802.2 (GND), U901.2 (GND), U902.2 (GND), U1001.2 (GND), U1002.2 (GND), U1101.2 (GND), U1102.2 (GND), U1201.2, U1202.7 (GND), U1203.3 (GND), U1204.3 (GND), U1301.2, U1302.7 (GND), U1303.3 (GND), U1304.3 (GND), U1401.2, U1402.7 (GND), U1403.3 (GND), U1404.3 (GND), U1601.16 (GND), U1701.16 (GND), U1801.1 (MODE_SYNC), U1801.9 (GND), U1802.2 (GND), U1802.5 (Pad), U1803.1 (GND), U1804.1 (GND), U1805.2 (GND), U1805.5 (Pad), U1806.2 (GND), U1806.5 (Pad), U2002.4 (V-), U2101.16 (GND), U2102.16 (GND), U2103.3 (NU), U2103.10 (GND), U2103.12 (ADDR0), U2103.13 (ADDR1), U2103.22 (VSYS), U2103.25 (GND), U2301.3 (VSS), U2301.7 (VSS), U2301.20 (LS_DAP), U2302.3 (VSS), U2302.7 (VSS), U2302.20 (LS_DAP), U2303.1 (GND), U2303.3 (ADD0), U2401.25 (VSS), U2402.2 (GND), X601.2 (VSS_), Y601.2 (GND), Y2401.2, Y2401.4
unnamed: C304.1, C306.1, L301.2, R304.1
unnamed: C502.1, T502.4
unnamed: C1605.1, L1601.2
unnamed: C1606.1, L1602.1
unnamed: C1607.1, L1603.1
unnamed: C1608.1, L1604.1
unnamed: C1609.1, L1605.1
unnamed: C1610.1, C1615.1, L1605.2, L1611.1
unnamed: C1611.1, C1616.1, L1607.2, L1609.1
unnamed: C1612.1, C1617.1, L1603.2, L1612.1
unnamed: C1613.1, C1618.1, L1606.1, L1608.2
unnamed: C1614.1, C1619.1, L1604.2, L1610.1
unnamed: C1620.1, C1623.1, L1611.2, L1615.1
unnamed: C1621.1, C1624.1, L1609.2, L1614.1
unnamed: C1622.1, C1626.1, L1610.2, L1616.1
unnamed: C1625.1, C1628.1, L1613.1, L1617.1
unnamed: C1627.1, C1629.1, L1612.2, L1619.1
unnamed: C1630.1, L1615.2
unnamed: C1631.1, L1616.2
unnamed: C1632.1, L1618.2
unnamed: C1633.1, L1620.2
unnamed: C1634.1, L1619.2
unnamed: C1805.1, C1806.1, L1801.2, R1801.2, R1803.2
unnamed: C1817.1, C1821.1, L1802.2, R1807.2, R1813.2
unnamed: C1818.1, C1822.1, L1803.2, R1809.2, R1814.2
unnamed: C2004.1, R2006.2
unnamed: C2115.2, R2104.2
unnamed: C2401.2, R2411.1, Y2401.3
unnamed: C2402.2, R2412.1, Y2401.1
unnamed: C2412.1, J2401.7
unnamed: C2006.1, C2007.1, D2001.2 (A), D2002.2 (A), IC2001.7 (DRVCC), U2001.1 (S), U2001.2 (S), U2001.3 (S)
unnamed: C2009.1, D2001.1 (K), IC2001.22 (BOOST2)
unnamed: C2010.2, D2002.1 (K), IC2001.36 (BOOST1)
unnamed: C2109.1, D2101.1 (K_1), J2101.A4 (VBUS_1), J2101.B4 (VBUS_2), Q2101.1 (S), Q2101.2 (S), Q2101.3 (S), R2101.1, R2102.1, U2103.24 (VDD)
unnamed: FB301.2, L301.1
unnamed: C2008.1, IC2001.3 (DRVSET), IC2001.8 (V5), IC2001.15 (MODE)
unnamed: IC2001.17 (FREQ), R2007.1
unnamed: C2002.1, IC2001.13 (ITH), R2006.1
unnamed: IC2001.6 (NDRV), U2001.4 (G)
unnamed: C2012.2, IC2001.34 (VIN), R2014.2
unnamed: IC2001.2 (VINOV), R2001.2, R2002.1
unnamed: IC2001.32 (VINSNS), R2012.2
unnamed: IC2001.30 (VOUTSNS), R2013.1
unnamed: C502.2, J501.1 (In)
unnamed: J2401.12, R2418.1
unnamed: J2401.14, R2419.1
unnamed: C2410.1, C2411.1, J2401.4 (TCT), J2401.5 (RCT)
unnamed: L402.2, R401.1
unnamed: L1601.1, L1606.2
unnamed: L1602.2, L1607.1
unnamed: L1608.1, L1613.2
unnamed: L1614.2, L1618.1
unnamed: L1617.2, L1620.1
unnamed: NT2001.1, R2015.2, R2019.2
unnamed: NT2001.2, Q2002.1 (S), Q2002.2 (S), Q2002.3 (S), Q2004.1 (S), Q2004.2 (S), Q2004.3 (S), R2021.2
unnamed: NT2002.1, R2016.2, R2020.2
unnamed: Q2001.4 (G), R2017.2
unnamed: Q2002.4 (G), R2018.2
unnamed: Q2003.4 (G), R2022.2
unnamed: Q2004.4 (G), R2023.2
unnamed: C2115.1, Q2101.5 (D), R2105.2, R2106.1
unnamed: Q2101.4 (G), R2102.2, R2103.1, R2104.1
unnamed: C2305.1, Q2301.3 (D), U2301.12 (HB)
unnamed: Q2301.1 (G), Q2304.1 (G), Q2304.5 (G), U2301.8 (LO)
unnamed: C2306.1, Q2302.3 (D), U2302.12 (HB)
unnamed: Q2302.1 (G), Q2306.1 (G), Q2306.5 (G), U2302.8 (LO)
unnamed: C2305.2, Q2303.3 (S), Q2303.4 (S), Q2303.6 (S), Q2304.2 (D), T2301.1, U2301.9 (HS), U2301.13 (HS), U2301.14 (HS), U2301.16 (HS), U2301.21 (HS_DAP)
unnamed: C2306.2, Q2305.3 (S), Q2305.4 (S), Q2305.6 (S), Q2306.2 (D), T2301.2, U2302.9 (HS), U2302.13 (HS), U2302.14 (HS), U2302.16 (HS), U2302.21 (HS_DAP)
unnamed: R301.1, R302.2, R303.2
unnamed: R502.1, T501.5
unnamed: R504.1, T501.4
unnamed: R801.1, R802.1, R803.1
unnamed: R901.1, R902.1, R903.1
unnamed: R1001.1, R1002.1, R1003.1
unnamed: R1101.1, R1102.1, R1103.1
unnamed: T301.4 (OUT1A), U303.3 (J2)
unnamed: C307.2, R304.2, T301.3 (OUT1B), T301.5 (OUT2B), T301.7 (OUT2B)
unnamed: PG201.1, U201.56 (PG0)
unnamed: PG202.1, U201.57 (PG1)
unnamed: PG203.1, U201.87 (PG2)
unnamed: PG204.1, U201.88 (PG3)
unnamed: PG205.1, U201.89 (PG4)
unnamed: PG206.1, U201.90 (PG5)
unnamed: PG207.1, U201.91 (PG6)
unnamed: PG208.1, U201.92 (PG7)
unnamed: PG209.1, U201.93 (PG8)
unnamed: PG210.1, U201.129 (PG14)
unnamed: PG211.1, U201.132 (PG15)
unnamed: C215.1, U201.71 (VCAP1)
unnamed: C213.1, U201.106 (VCAP2)
unnamed: C303.1, R303.1, U301.3 (+)
unnamed: FB301.1, U301.1, U301.2 (-)
unnamed: T301.6 (OUT2A), U304.3 (J2)
unnamed: T301.8 (OUT2A), U305.3 (J2)
unnamed: C318.2, C319.2, U306.27 (VDD18)
unnamed: C405.1, U405.5 (J1)
unnamed: C408.1, U406.5 (J1)
unnamed: C409.1, U408.5 (J1)
unnamed: C410.1, U409.5 (J1)
unnamed: C411.1, U410.5 (J1)
unnamed: U411.5 (J1), U413.1 (J3), U416.3 (J2)
unnamed: C412.1, U412.5 (J1)
unnamed: L402.1, U413.5 (J1)
unnamed: C413.1, U414.5 (J1)
unnamed: L403.1, U415.5 (J1)
unnamed: L403.2, U416.5 (J1)
unnamed: C414.1, U417.5 (J1)
unnamed: L404.1, U418.5 (J1)
unnamed: C415.1, U419.5 (J1)
unnamed: L405.1, U420.5 (J1)
unnamed: C416.1, U421.5 (J1)
unnamed: C417.1, U422.5 (J1)
unnamed: R601.2, U601.3 (EN)
unnamed: U602.44 (IOB_3b_G6), Y601.3 (OUTPUT)
unnamed: C607.2, C609.2, R602.2, U602.29 (VCCPLL)
unnamed: R801.2, U801.3 (J2)
unnamed: U801.1 (J3), U802.1 (J3)
unnamed: R803.2, U802.3 (J2)
unnamed: R901.2, U901.3 (J2)
unnamed: U901.1 (J3), U902.1 (J3)
unnamed: R903.2, U902.3 (J2)
unnamed: R1001.2, U1001.3 (J2)
unnamed: U1001.1 (J3), U1002.1 (J3)
unnamed: R1003.2, U1002.3 (J2)
unnamed: R1101.2, U1101.3 (J2)
unnamed: U1101.1 (J3), U1102.1 (J3)
unnamed: R1103.2, U1102.3 (J2)
unnamed: C1207.1, C1214.1, R1203.1, U1202.2 (COM1)
unnamed: C1208.1, C1211.1, R1204.1, U1202.4 (COM2)
unnamed: C1204.1, C1206.1, R1201.1, U1202.9 (COM3)
unnamed: C1203.1, C1205.1, R1202.1, U1202.10 (COM4)
unnamed: C1207.2, U1203.5 (INA+)
unnamed: C1204.2, U1203.4 (INA-)
unnamed: R1205.2, R1206.1, U1203.7 (INB)
unnamed: R1205.1, R1209.1, U1203.8 (OUTA)
unnamed: R1206.2, R1210.1, U1203.6 (OUTB)
unnamed: C1208.2, U1204.5 (INA+)
unnamed: C1205.2, U1204.4 (INA-)
unnamed: R1207.2, R1208.1, U1204.7 (INB)
unnamed: R1207.1, R1211.1, U1204.8 (OUTA)
unnamed: R1208.2, R1212.1, U1204.6 (OUTB)
unnamed: C1307.1, C1314.1, R1303.1, U1302.2 (COM1)
unnamed: C1308.1, C1311.1, R1304.1, U1302.4 (COM2)
unnamed: C1304.1, C1306.1, R1301.1, U1302.9 (COM3)
unnamed: C1303.1, C1305.1, R1302.1, U1302.10 (COM4)
unnamed: C1307.2, U1303.5 (INA+)
unnamed: C1304.2, U1303.4 (INA-)
unnamed: R1305.2, R1306.1, U1303.7 (INB)
unnamed: R1305.1, R1309.1, U1303.8 (OUTA)
unnamed: R1306.2, R1310.1, U1303.6 (OUTB)
unnamed: C1308.2, U1304.5 (INA+)
unnamed: C1305.2, U1304.4 (INA-)
unnamed: R1307.2, R1308.1, U1304.7 (INB)
unnamed: R1307.1, R1311.1, U1304.8 (OUTA)
unnamed: R1308.2, R1312.1, U1304.6 (OUTB)
unnamed: C1407.1, C1414.1, R1403.1, U1402.2 (COM1)
unnamed: C1408.1, C1411.1, R1404.1, U1402.4 (COM2)
unnamed: C1404.1, C1406.1, R1401.1, U1402.9 (COM3)
unnamed: C1403.1, C1405.1, R1402.1, U1402.10 (COM4)
unnamed: C1407.2, U1403.5 (INA+)
unnamed: C1404.2, U1403.4 (INA-)
unnamed: R1405.2, R1406.1, U1403.7 (INB)
unnamed: R1405.1, R1409.1, U1403.8 (OUTA)
unnamed: R1406.2, R1410.1, U1403.6 (OUTB)
unnamed: C1408.2, U1404.5 (INA+)
unnamed: C1405.2, U1404.4 (INA-)
unnamed: R1407.2, R1408.1, U1404.7 (INB)
unnamed: R1407.1, R1411.1, U1404.8 (OUTA)
unnamed: R1408.2, R1412.1, U1404.6 (OUTB)
unnamed: K1601.12, U1601.3 (DRAIN0)
unnamed: K1602.12, U1601.4 (DRAIN1)
unnamed: K1603.12, U1601.5 (DRAIN2)
unnamed: K1604.12, U1601.6 (DRAIN3)
unnamed: K1605.12, U1601.11 (DRAIN4)
unnamed: K1701.12, U1701.3 (DRAIN0)
unnamed: K1702.12, U1701.4 (DRAIN1)
unnamed: K1703.12, U1701.5 (DRAIN2)
unnamed: K1704.12, U1701.6 (DRAIN3)
unnamed: K1705.12, U1701.11 (DRAIN4)
unnamed: K1706.12, U1701.12 (DRAIN5)
unnamed: K1707.12, U1701.13 (DRAIN6)
unnamed: K1708.12, U1701.14 (DRAIN7)
unnamed: C1804.1, U1801.6 (BOOT)
unnamed: C1804.2, L1801.1, U1801.5 (SW)
unnamed: C1803.1, U1801.7 (VCC)
unnamed: R1801.1, R1802.2, U1801.8 (VOUT_FB)
unnamed: C1812.1, R1804.2, U1802.1 (OUT)
unnamed: C1815.1, U1803.6 (CB)
unnamed: R1807.1, R1808.2, U1803.4 (FB)
unnamed: C1815.2, L1802.1, U1803.2 (SW)
unnamed: C1816.1, U1804.6 (CB)
unnamed: R1809.1, R1810.2, U1804.4 (FB)
unnamed: C1816.2, L1803.1, U1804.2 (SW)
unnamed: R1805.2, U1805.3 (EN)
unnamed: C1819.1, R1811.2, U1805.1 (OUT)
unnamed: R1806.2, U1806.3 (EN)
unnamed: C1820.1, R1812.2, U1806.1 (OUT)
unnamed: R2009.1, R2010.2, U2002.3 (+)
unnamed: C2011.1, R2008.2, R2011.1, U2002.2 (-)
unnamed: R2003.1, R2004.2, U2002.5 (+)
unnamed: K2101.12, U2101.3 (DRAIN0)
unnamed: K2102.12, U2101.4 (DRAIN1)
unnamed: K2103.12, U2101.5 (DRAIN2)
unnamed: K2104.12, U2101.6 (DRAIN3)
unnamed: K2105.12, U2101.11 (DRAIN4)
unnamed: K2106.12, U2101.12 (DRAIN5)
unnamed: K2107.12, U2101.13 (DRAIN6)
unnamed: K2108.12, U2101.14 (DRAIN7)
unnamed: U2101.9 (SER_OUT), U2102.2 (SER_IN)
unnamed: K2109.12, U2102.3 (DRAIN0)
unnamed: R2106.2, U2103.9 (DISCH)
unnamed: R2103.2, U2103.16 (VBUS_EN_SNK)
unnamed: C2111.1, U2103.21 (VREG_1V2)
unnamed: Q2303.1 (G), Q2303.5 (G), U2301.10 (HO)
unnamed: Q2305.1 (G), Q2305.5 (G), U2302.10 (HO)
unnamed: R2405.2, R2408.1, U2401.11 (CRS_DV/MODE2)
unnamed: R2415.2, U2401.24 (RBIAS)
unnamed: R2403.2, R2410.1, U2401.8 (RXD0/MODE0)
unnamed: R2404.2, R2409.1, U2401.7 (RXD1/MODE1)
unnamed: R2401.2, U2401.10 (RXER/PHYAD0)
unnamed: C2404.1, C2405.1, U2401.6 (VDDCR)
unnamed: R2411.2, U2401.5 (XTAL1/CLKIN)
unnamed: R2412.2, U2401.4 (XTAL2)
unnamed: R2402.2, R2406.1, U2401.14 (~INT/REFCLKO)
VBUS: C1801.1, C1802.1, C1808.1, C1809.1, C1810.1, C1811.1, C2014.1, C2015.1, C2017.1, C2018.1, C2019.1, C2020.1, C2022.1, D2101.3 (K_2), Q2001.5 (D), R2012.1, R2014.1, R2105.1, U1801.4 (VIN), U1803.3 (VIN), U1803.5 (EN), U1804.3 (VIN), U2001.5 (D), U2001.6 (D), U2001.7 (D), U2001.8 (D)
Veer: C2021.1, C2023.1, Q2003.5 (D), Q2303.2 (D), Q2305.2 (D), R2001.1, R2003.2, R2009.2, R2013.2
nRESET: J202.10 (~RESET), U201.25 (NRST), U407.18 (~RESET), U2401.15 (~RST)
